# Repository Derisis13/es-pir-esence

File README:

# ES-PIR-esence

A small circuit to detect presence with an ESP8266 module and a PIR sensor.
My idea is to use ESPHome to connect the circuit to HomeAssistant for home automation or security.

---

ES-PIR-esence (c) by HA5PLS

ES-PIR-esence is licensed under a
Creative Commons Attribution-ShareAlike 4.0 International License.

You should have received a copy of the license along with this
work. If not, see <http://creativecommons.org/licenses/by-sa/4.0/>.

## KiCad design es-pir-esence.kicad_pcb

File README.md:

# ES-PIR-esence

A small circuit to detect presence with an ESP8266 module and a PIR sensor.
My idea is to use ESPHome to connect the circuit to HomeAssistant for home automation or security.

Schematic:

Layout:

---

ES-PIR-esence (c) by HA5PLS

ES-PIR-esence is licensed under a
Creative Commons Attribution-ShareAlike 4.0 International License.

You should have received a copy of the license along with this
work. If not, see <http://creativecommons.org/licenses/by-sa/4.0/>.

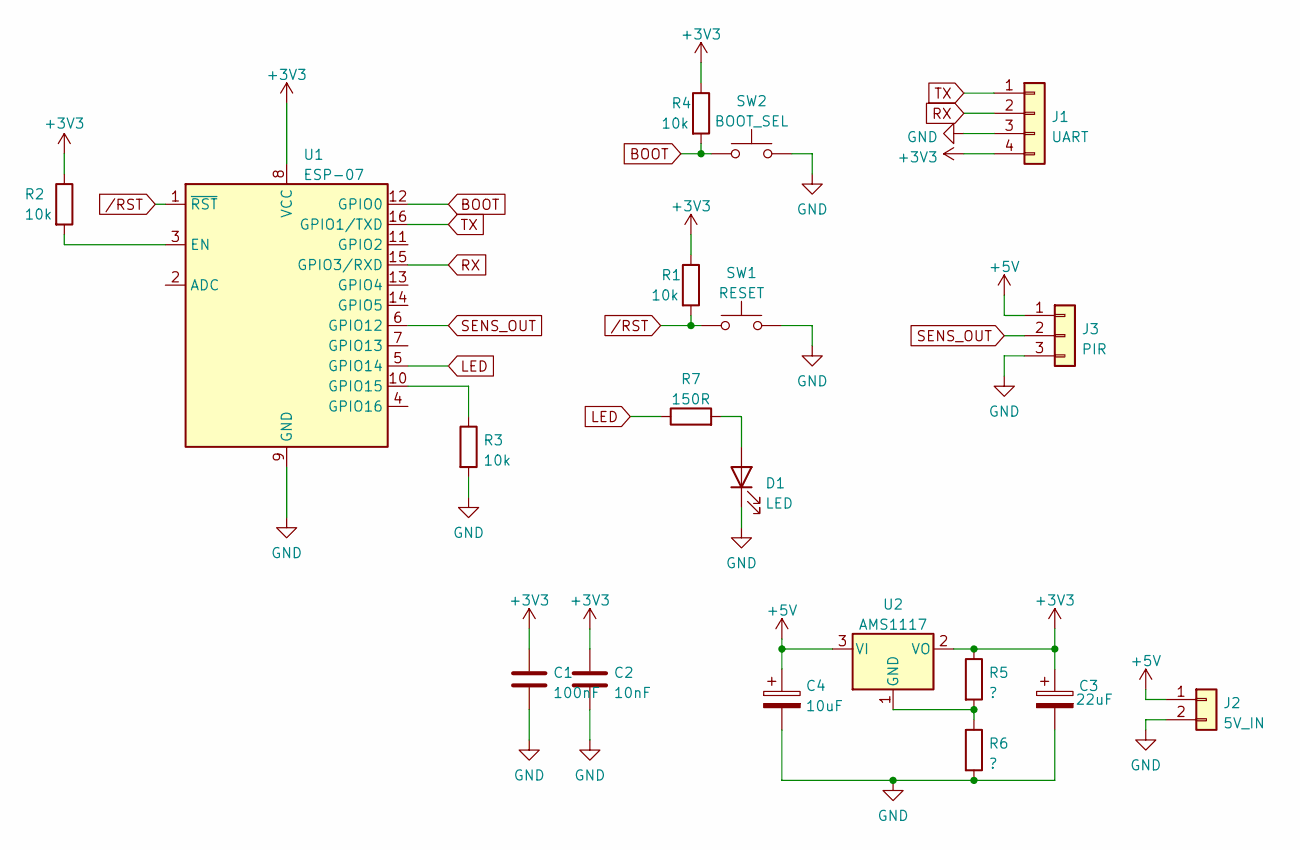
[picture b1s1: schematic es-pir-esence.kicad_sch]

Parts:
C1: 100nF; C_0805_2012Metric_Pad1.18x1.45mm_HandSolder
C2: 10nF; C_0805_2012Metric_Pad1.18x1.45mm_HandSolder
C3: 22uF; CP_EIA-3528-21_Kemet-B_Pad1.50x2.35mm_HandSolder
C4: 10uF; CP_Radial_D4.0mm_P2.00mm
D1: LED; LED_0805_2012Metric_Pad1.15x1.40mm_HandSolder
J1: UART; PinHeader_1x04_P2.54mm_Vertical
J2: 5V_IN; PinHeader_1x02_P2.54mm_Vertical
J3: PIR; PinSocket_1x03_P2.54mm_Vertical
R1, R2, R3, R4: 10k; R_0805_2012Metric_Pad1.20x1.40mm_HandSolder
R5, R6: ?; R_0805_2012Metric_Pad1.20x1.40mm_HandSolder
R7: 150R; R_0805_2012Metric_Pad1.20x1.40mm_HandSolder
SW1: RESET; SW_PUSH_6mm
SW2: BOOT_SEL; SW_PUSH_6mm
U1: ESP-07
U2: AMS1117; SOT-223-3_TabPin2

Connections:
+3V3: C1.1, C2.1, C3.1, J1.4, R1.1, R2.1, R4.1, R5.1, U1.8 (VCC), U2.2 (VO)
+5V: C4.1, J2.1, J3.1, U2.3 (VI)
BOOT: R4.2, SW2.1, U1.12 (GPIO0)
GND: C1.2, C2.2, C3.2, C4.2, D1.1 (K), J1.3, J2.2, J3.3, R3.2, R6.2, SW1.2, SW2.2, U1.9 (GND)
LED: R7.1, U1.5 (GPIO14)
unnamed: D1.2 (A), R7.2
unnamed: R2.2, U1.3 (EN)
unnamed: R3.1, U1.10 (GPIO15)
unnamed: R5.2, R6.1, U2.1 (GND)
RX: J1.2, U1.15 (GPIO3/RXD)
SENS_OUT: J3.2, U1.6 (GPIO12)
TX: J1.1, U1.16 (GPIO1/TXD)
/RST: R1.2, SW1.1, U1.1 (~RST)

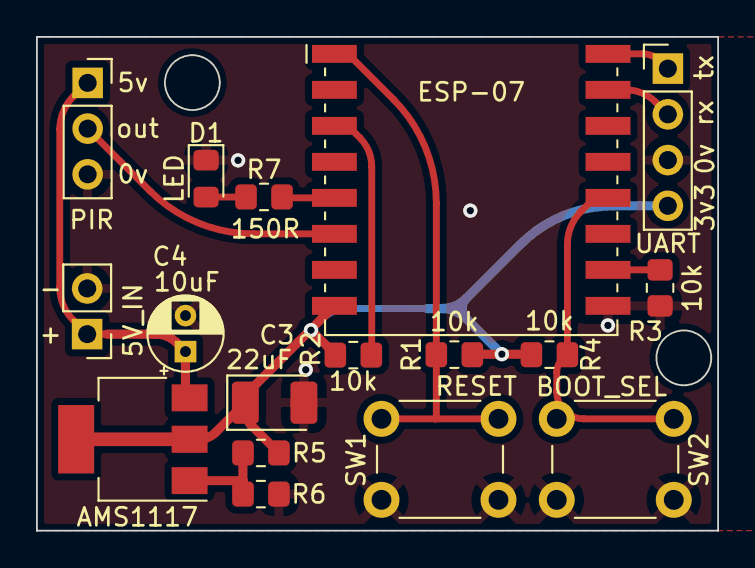
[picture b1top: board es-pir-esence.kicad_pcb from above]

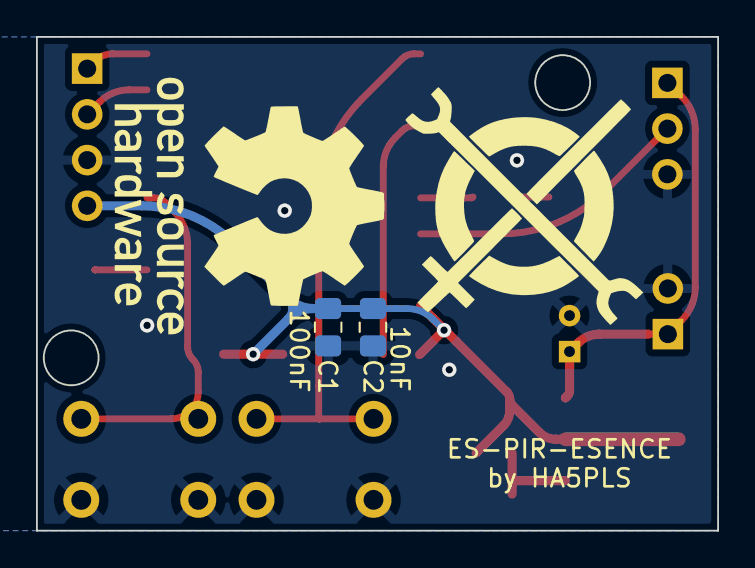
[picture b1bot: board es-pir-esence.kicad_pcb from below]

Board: 2 copper layers, 37.8 x 27.4 mm, 19 parts (2 on the bottom side), 13 nets.

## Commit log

2022-09-22 Ver. 1.0 by HA5PLS
    Special thanks to:
    - [HA5ERI](https://github.com/KeriBoti): schematic review, layout review and suggestion
    - ESPHome Discord community: layout review
2022-09-22 Readme and LICENSE
2022-09-22 README -> README.md
2022-09-22 fix missing A
    (vim pasting things)
2022-09-27 Improve high frequency response of PCB
2022-10-11 Added previews for schematic and layout
